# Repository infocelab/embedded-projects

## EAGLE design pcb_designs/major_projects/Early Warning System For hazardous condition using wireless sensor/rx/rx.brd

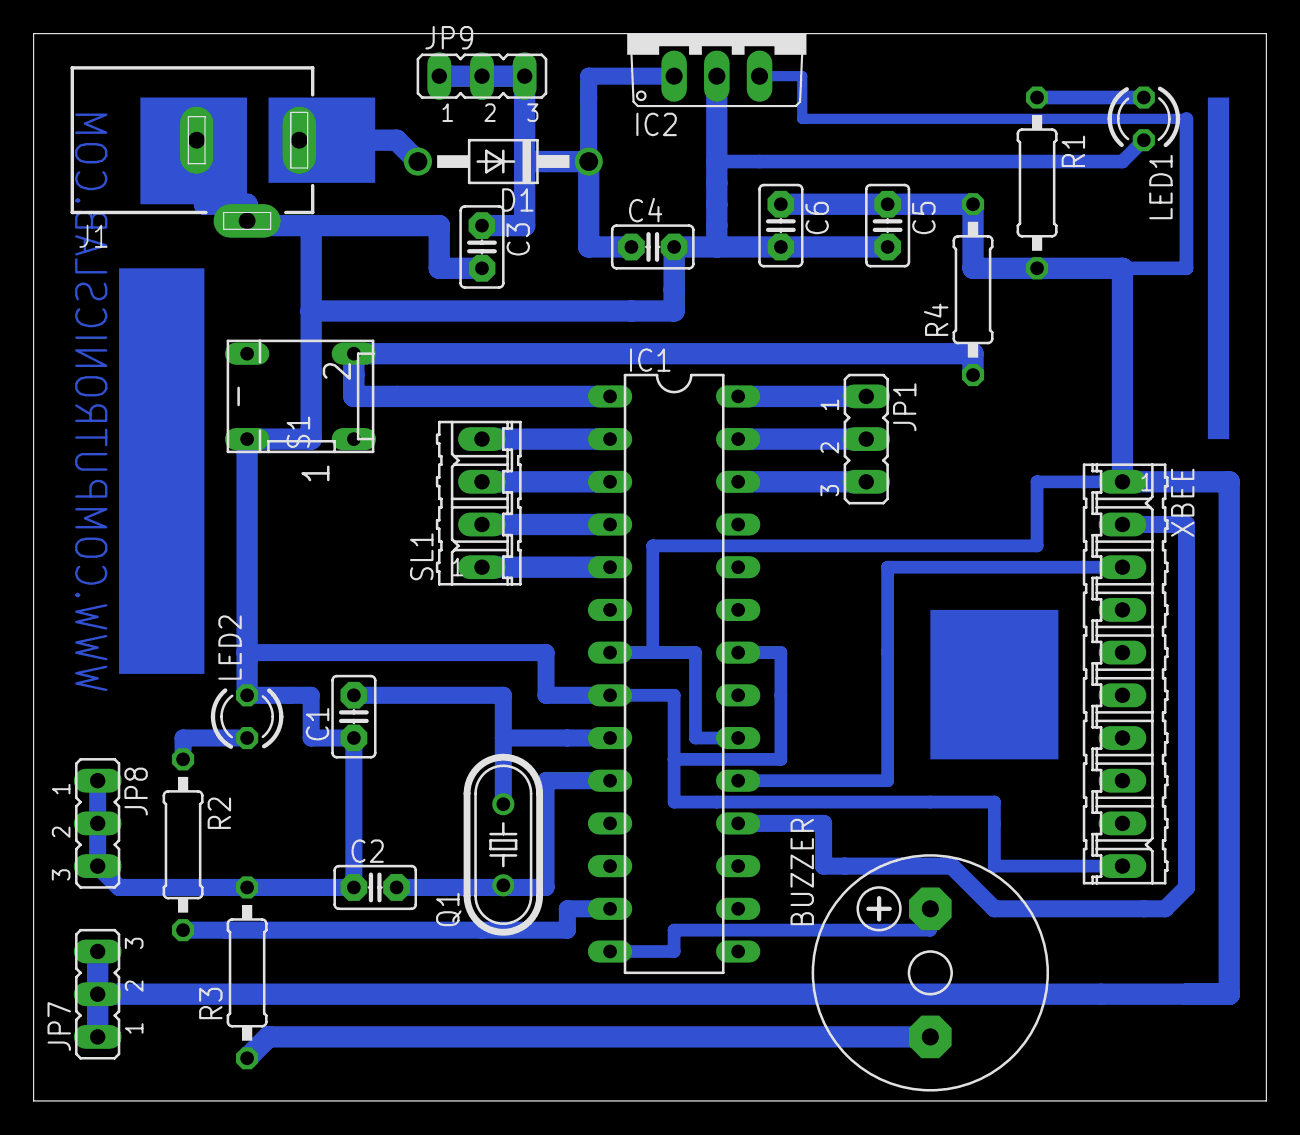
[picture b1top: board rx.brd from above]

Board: 2 copper layers, 73.3 x 63.5 mm, 25 parts (0 on the bottom side), 21 nets.

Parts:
BUZZER: F/CM12P
C1, C2: 22pf; C2.5-2
C3: 100UF; C2.5-2
C4, C5: 0.1uf; C2.5-2
C6: 4.7uf; C2.5-2
D1: 1N4007; DO41-10
IC1: ATMEGA328; DIL28-3
IC2: 7805; TO220V
J1: DCJ0303
JP1, JP7, JP8, JP9: JP2
LED1, LED2: LED3MM
Q1: 16MHZ; HC49/S
R1: 220R; 0207/10
R2: 330R; 0207/10
R3, R4: 10K; 0207/10
S1: DP-02
SL1: 04P
XBEE: 10P

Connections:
unnamed: C1.2, IC1.9, Q1.2
unnamed: C2.2, IC1.10, Q1.1
unnamed: D1.A, J1.1
unnamed: C5.1, C6.1, IC1.7, IC1.20, IC2.3, JP7.1, JP7.2, JP7.3, R1.2, R4.2, XBEE.1
unnamed: C1.1, C2.1, C3.2, C4.2, C5.2, C6.2, IC1.8, IC1.22, IC2.2, J1.2, J1.3, JP8.1, JP8.2, JP8.3, LED1.K, LED2.K, R3.2, S1.4, XBEE.10
unnamed: LED1.A, R1.1
unnamed: C3.1, C4.1, D1.C, IC2.1, JP9.1, JP9.2, JP9.3
unnamed: IC1.28, JP1.1
unnamed: IC1.27, JP1.2
unnamed: IC1.26, JP1.3
unnamed: IC1.18, XBEE.2
unnamed: IC1.19, XBEE.3
unnamed: BUZZER.-, R3.1
unnamed: IC1.5, SL1.1
unnamed: IC1.2, SL1.4
unnamed: IC1.3, SL1.3
unnamed: IC1.4, SL1.2
unnamed: BUZZER.+, IC1.14
unnamed: IC1.13, R2.2
unnamed: IC1.1, R4.1, S1.2
unnamed: LED2.A, R2.1

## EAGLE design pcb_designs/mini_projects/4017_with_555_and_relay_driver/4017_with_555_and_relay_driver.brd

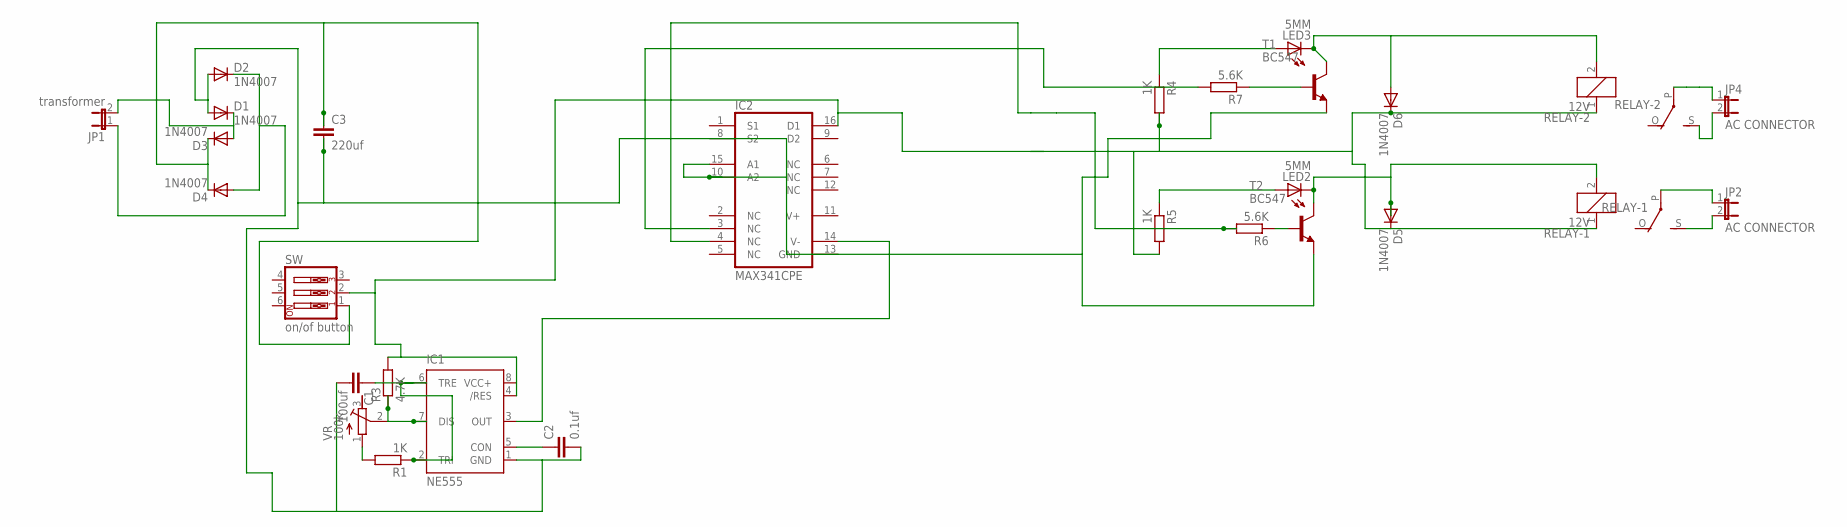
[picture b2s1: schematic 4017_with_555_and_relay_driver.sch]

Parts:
C1: 100uf; C025-050X050
C2: 0.1uf; C025-050X050
C3: 220uf; C5B7.2
D1, D2, D3, D4, D5, D6: 1N4007; DO41-10
IC1: NE555; DIL-08
IC2: MAX341CPE; DIL16
JP1: transformer; JP1
JP2, JP4: AC CONNECTOR; JP1
LED2, LED3: 5MM; LED5MM
R1, R4, R5: 1K; 0204/7
R3: 4.7K; 0204/7
R6, R7: 5.6K; 0204/7
RELAY-1, RELAY-2: 12V; G5LE
SW: on/of button; EDG-03
T1, T2: BC547; TO92
VR: 100k; RTRIM64P

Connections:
unnamed: C1.1, IC1.2 (TRI), IC1.6 (TRE), R1.1
unnamed: C2.1, IC1.5 (CON)
unnamed: IC1.7 (DIS), R3.1, VR.2 (S)
unnamed: IC1.3 (OUT), IC2.14 (V-)
unnamed: IC1.4 (/RES), IC1.8 (VCC+), IC2.16 (D1), R3.2, SW.2
unnamed: D5.C, D6.C, R4.2, R5.2, RELAY-1.1, RELAY-2.1
unnamed: R1.2, VR.1 (E)
unnamed: C1.2, C2.2, C3.2, D1.A, D2.A, IC1.1 (GND), IC2.8 (S2), IC2.10 (A2), IC2.13 (GND), IC2.15 (A1), T1.1 (E), T2.1 (E)
unnamed: C3.1, D3.C, D4.C, SW.1
unnamed: D2.C, D4.A, JP1.1
unnamed: D1.C, D3.A, JP1.2
unnamed: D5.A, LED2.K (C), RELAY-1.2, T2.3 (C)
unnamed: R7.1, T1.2 (B)
unnamed: R6.1, T2.2 (B)
unnamed: LED2.A, R5.1
unnamed: LED3.A, R4.1
unnamed: JP2.2, RELAY-1.S
unnamed: JP2.1, RELAY-1.P
unnamed: JP4.2, RELAY-2.S
unnamed: JP4.1, RELAY-2.P
unnamed: IC2.4 (NC), R6.2
unnamed: IC2.3 (NC), R7.2
unnamed: D6.A, LED3.K (C), RELAY-2.2, T1.3 (C)
V+: IC2.11 (V+)

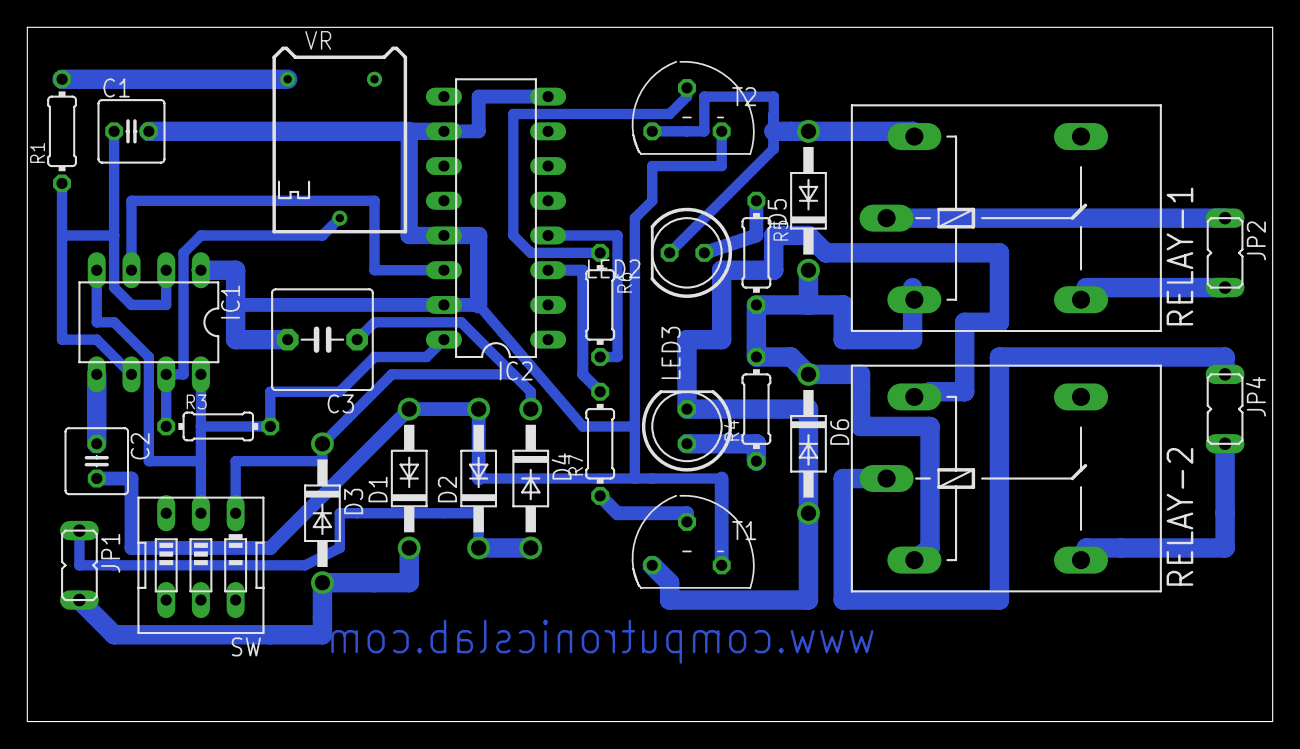
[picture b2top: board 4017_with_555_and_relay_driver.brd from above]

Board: 2 copper layers, 91.1 x 50.8 mm, 28 parts (0 on the bottom side), 23 nets.

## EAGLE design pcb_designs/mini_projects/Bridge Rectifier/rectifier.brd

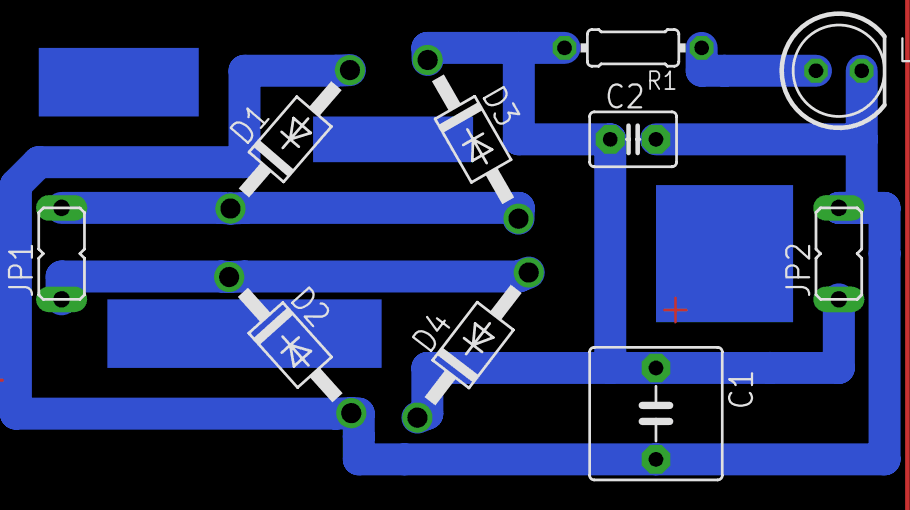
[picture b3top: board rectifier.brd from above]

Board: 2 copper layers, 10 parts (0 on the bottom side), 5 nets.

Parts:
C1: 220uf; C5B7.2
C2: 0.1uf; C2.5-3
D1, D2, D3, D4: 1N4007; DO41-10
JP1: transformer; JP1
JP2: output; JP1
LED1: 5mm; LED5MM
R1: 0204/7

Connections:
unnamed: C1.2, C2.2, D1.A, D2.A, JP2.2, LED1.K
unnamed: C1.1, C2.1, D3.C, D4.C, JP2.1, R1.2
unnamed: D2.C, D4.A, JP1.1
unnamed: D1.C, D3.A, JP1.2
unnamed: LED1.A, R1.1

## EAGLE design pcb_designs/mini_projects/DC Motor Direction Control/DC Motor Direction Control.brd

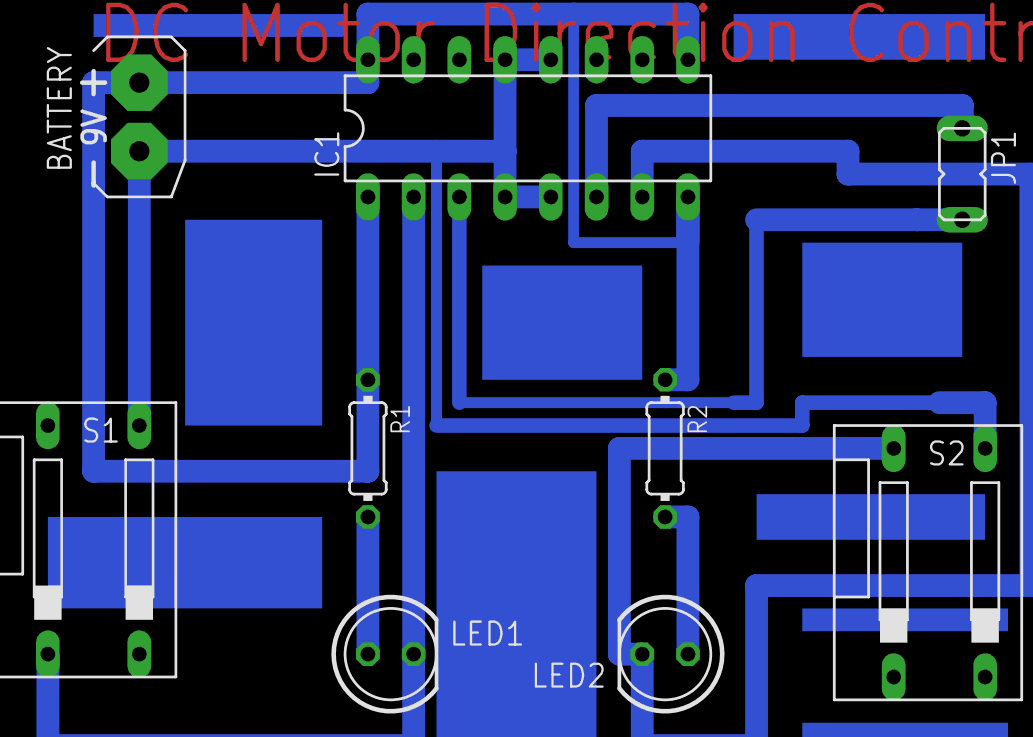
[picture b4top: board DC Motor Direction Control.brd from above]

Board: 2 copper layers, 9 parts (0 on the bottom side), 8 nets.

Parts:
BATTERY: 9V; AB9V
IC1: L293D; DIL16
JP1: motor; JP1
LED1, LED2: 5mm; LED5MM
R1, R2: 330E; 0204/7
S1, S2: push switch; DS-02

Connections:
unnamed: BATTERY.-, IC1.4, IC1.5, IC1.12, IC1.13, S1.3, S2.3
unnamed: IC1.2, LED1.K, S1.1
unnamed: BATTERY.+, IC1.1, IC1.8, IC1.9, IC1.16, R1.1, R2.1
unnamed: IC1.6, JP1.1
unnamed: LED2.A, R2.2
unnamed: LED1.A, R1.2
unnamed: IC1.3, JP1.2
unnamed: IC1.7, LED2.K, S2.4

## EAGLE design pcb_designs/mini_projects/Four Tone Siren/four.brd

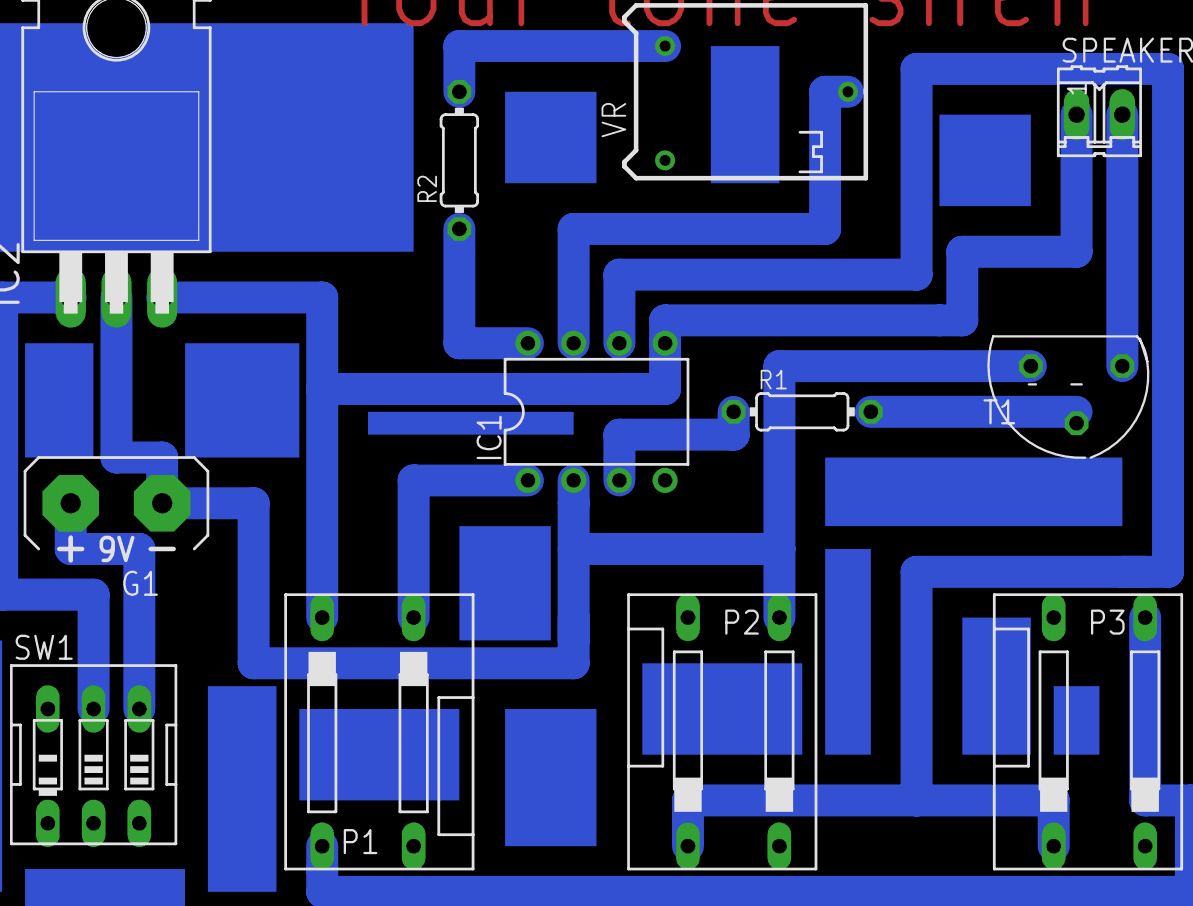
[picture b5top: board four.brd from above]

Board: 2 copper layers, 12 parts (0 on the bottom side), 13 nets.

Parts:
G1: AB9V
IC1: UM3561; DIL08
IC2: 7805T; TO220H
P1: push switch1; DS-02
P2: push swich2; DS-02
P3: push switch3; DS-02
R1: 10k; 0204/7
R2: 150k; 0204/7
SPEAKER: 8ohms; 02P
SW1: on/off switch; EDG-03
T1: BC547; TO92
VR: 100k; RTRIM64P

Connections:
unnamed: IC1.3, R1.1
unnamed: R1.2, T1.2
unnamed: SPEAKER.2, T1.3
unnamed: IC1.8, R2.1
unnamed: R2.2, VR.3
unnamed: IC1.7, VR.2
unnamed: IC2.1, SW1.5
unnamed: G1.-, IC1.2, IC2.2, P2.3, T1.1
unnamed: IC1.6, P2.1, P3.1
unnamed: IC1.5, IC2.3, P1.2, SPEAKER.1
unnamed: IC1.1, P1.1
unnamed: P1.3, P3.3
unnamed: G1.+, SW1.4

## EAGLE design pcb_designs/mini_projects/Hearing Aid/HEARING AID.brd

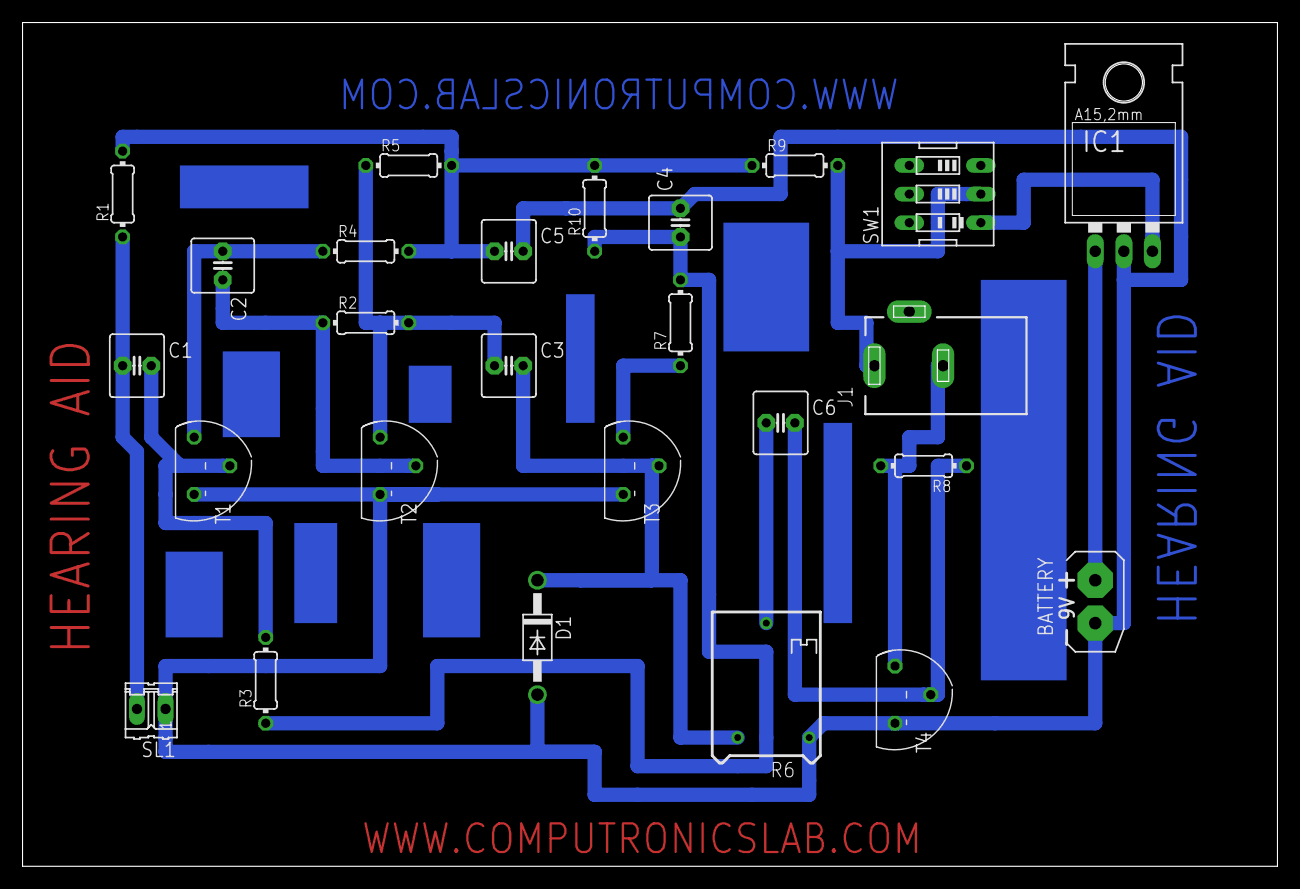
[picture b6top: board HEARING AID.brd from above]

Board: 2 copper layers, 111.4 x 74.9 mm, 26 parts (0 on the bottom side), 16 nets.

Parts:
BATTERY: 9V; AB9V
C1, C2: 0.1uf; C2.5-6
C3, C6: 1uf; C2.5-6
C4: 10uf; C2.5-6
C5: 100uf; C2.5-6
D1: 1N4007; DO41-10
IC1: 7805; 78XXL
J1: DCJ0202
R1, R8: 10K; 0204/7
R2, R10: 100k; 0204/7
R3: 1M; 0204/7
R4: 4.7K; 0204/7
R5: 3.9K; 0204/7
R6: 22K; RTRIM64P
R7: 1.5K; 0204/7
R9: 100E; 0204/7
SL1: electret mic; 02P
SW1: on/off switch; EDG-03
T1, T2, T3, T4: BC547; TO92

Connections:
unnamed: C1.2, R3.2, T1.2
unnamed: C1.1, R1.1, SL1.2
unnamed: C2.1, R4.1, T1.3
unnamed: C2.2, R2.1, T2.2
unnamed: C3.1, R2.2, R5.1, T2.3
unnamed: C3.2, D1.C, R6.3, T3.2
unnamed: R7.1, T3.3
unnamed: C4.1, R3.1, R7.2, R10.1
unnamed: C5.1, R1.2, R4.2, R5.2, R9.1, R10.2
unnamed: C6.1, R6.2
unnamed: C6.2, R8.1, T4.2
unnamed: J1.3, R8.2, T4.3
unnamed: BATTERY.+, IC1.IN
unnamed: BATTERY.-, C4.2, C5.2, D1.A, IC1.GND, R6.1, SL1.1, T1.1, T2.1, T3.1, T4.1
unnamed: IC1.OUT, SW1.1
unnamed: J1.1, R9.2, SW1.2

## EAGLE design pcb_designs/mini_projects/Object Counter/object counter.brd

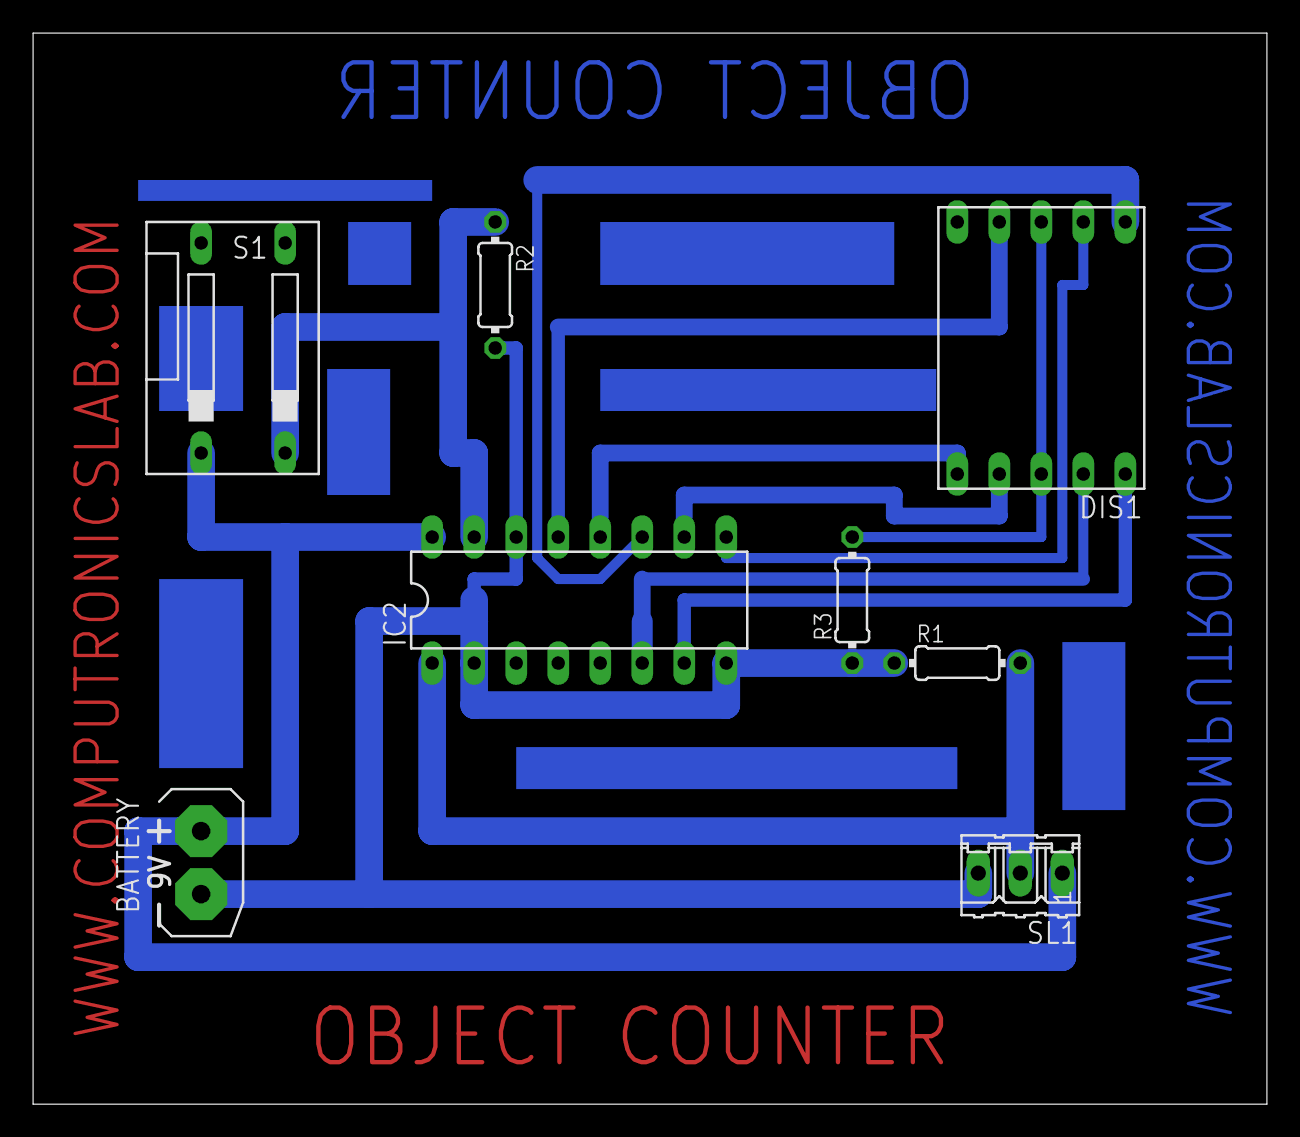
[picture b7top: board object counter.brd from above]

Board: 2 copper layers, 74.6 x 64.8 mm, 8 parts (0 on the bottom side), 12 nets.

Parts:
BATTERY: 9V; AB9V
DIS1: COMMON CATHODE; HDSP-M
IC2: 4033; DIL16
R1: 33K; 0204/7
R2: 47K; 0204/7
R3: 470E; 0204/7
S1: PUSH SWITCH; DS-02
SL1: IR MODULE; 03P

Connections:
unnamed: BATTERY.-, IC2.2, IC2.8, IC2.14, R1.1, R2.2, R3.1, SL1.3
unnamed: BATTERY.+, IC2.16, S1.1, SL1.1
unnamed: DIS1.3, DIS1.8, R3.2
unnamed: IC2.1, R1.2, SL1.2
unnamed: DIS1.7, IC2.10
unnamed: DIS1.6, IC2.12
unnamed: DIS1.4, IC2.13
unnamed: DIS1.2, IC2.9
unnamed: DIS1.1, IC2.11
unnamed: DIS1.9, IC2.6
unnamed: DIS1.10, IC2.7
unnamed: IC2.15, R2.1, S1.2

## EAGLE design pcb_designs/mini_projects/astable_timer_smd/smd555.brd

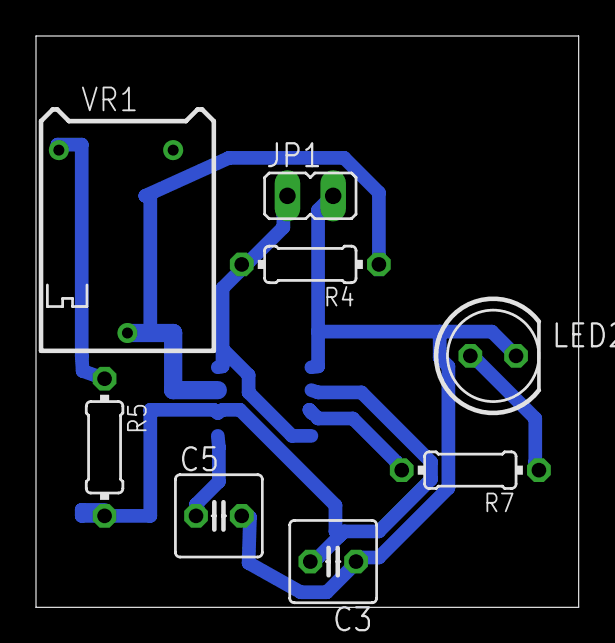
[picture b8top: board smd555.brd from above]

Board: 2 copper layers, 30.1 x 31.7 mm, 9 parts (1 on the bottom side), 8 nets.

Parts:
C3: 100UF; C025-050X050
C5: 0.1UF; C025-050X050
IC2: SE555D; SO08
JP1: JP1
LED2: 5mm; LED5MM
R4: 4.7K; 0204/7
R5: 1K; 0204/7
R7: 220E; 0204/7
VR1: 100k; RTRIM64P

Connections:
+5V: IC2.4, IC2.8, JP1.1, R4.2
GND: C3.1, C5.2, IC2.1, JP1.2, LED2.K
unnamed: IC2.3, R7.2
unnamed: C5.1, IC2.5
unnamed: LED2.A, R7.1
unnamed: C3.2, IC2.2, IC2.6, R5.2
unnamed: R5.1, VR1.1
unnamed: IC2.7, R4.1, VR1.2
